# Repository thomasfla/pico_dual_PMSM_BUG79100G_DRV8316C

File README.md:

# pico_dual_PMSM_BUG79100G_DRV8316C
Low cost PMSM using RPI Pico, external ADC and integrated mos+driver+current sensing.

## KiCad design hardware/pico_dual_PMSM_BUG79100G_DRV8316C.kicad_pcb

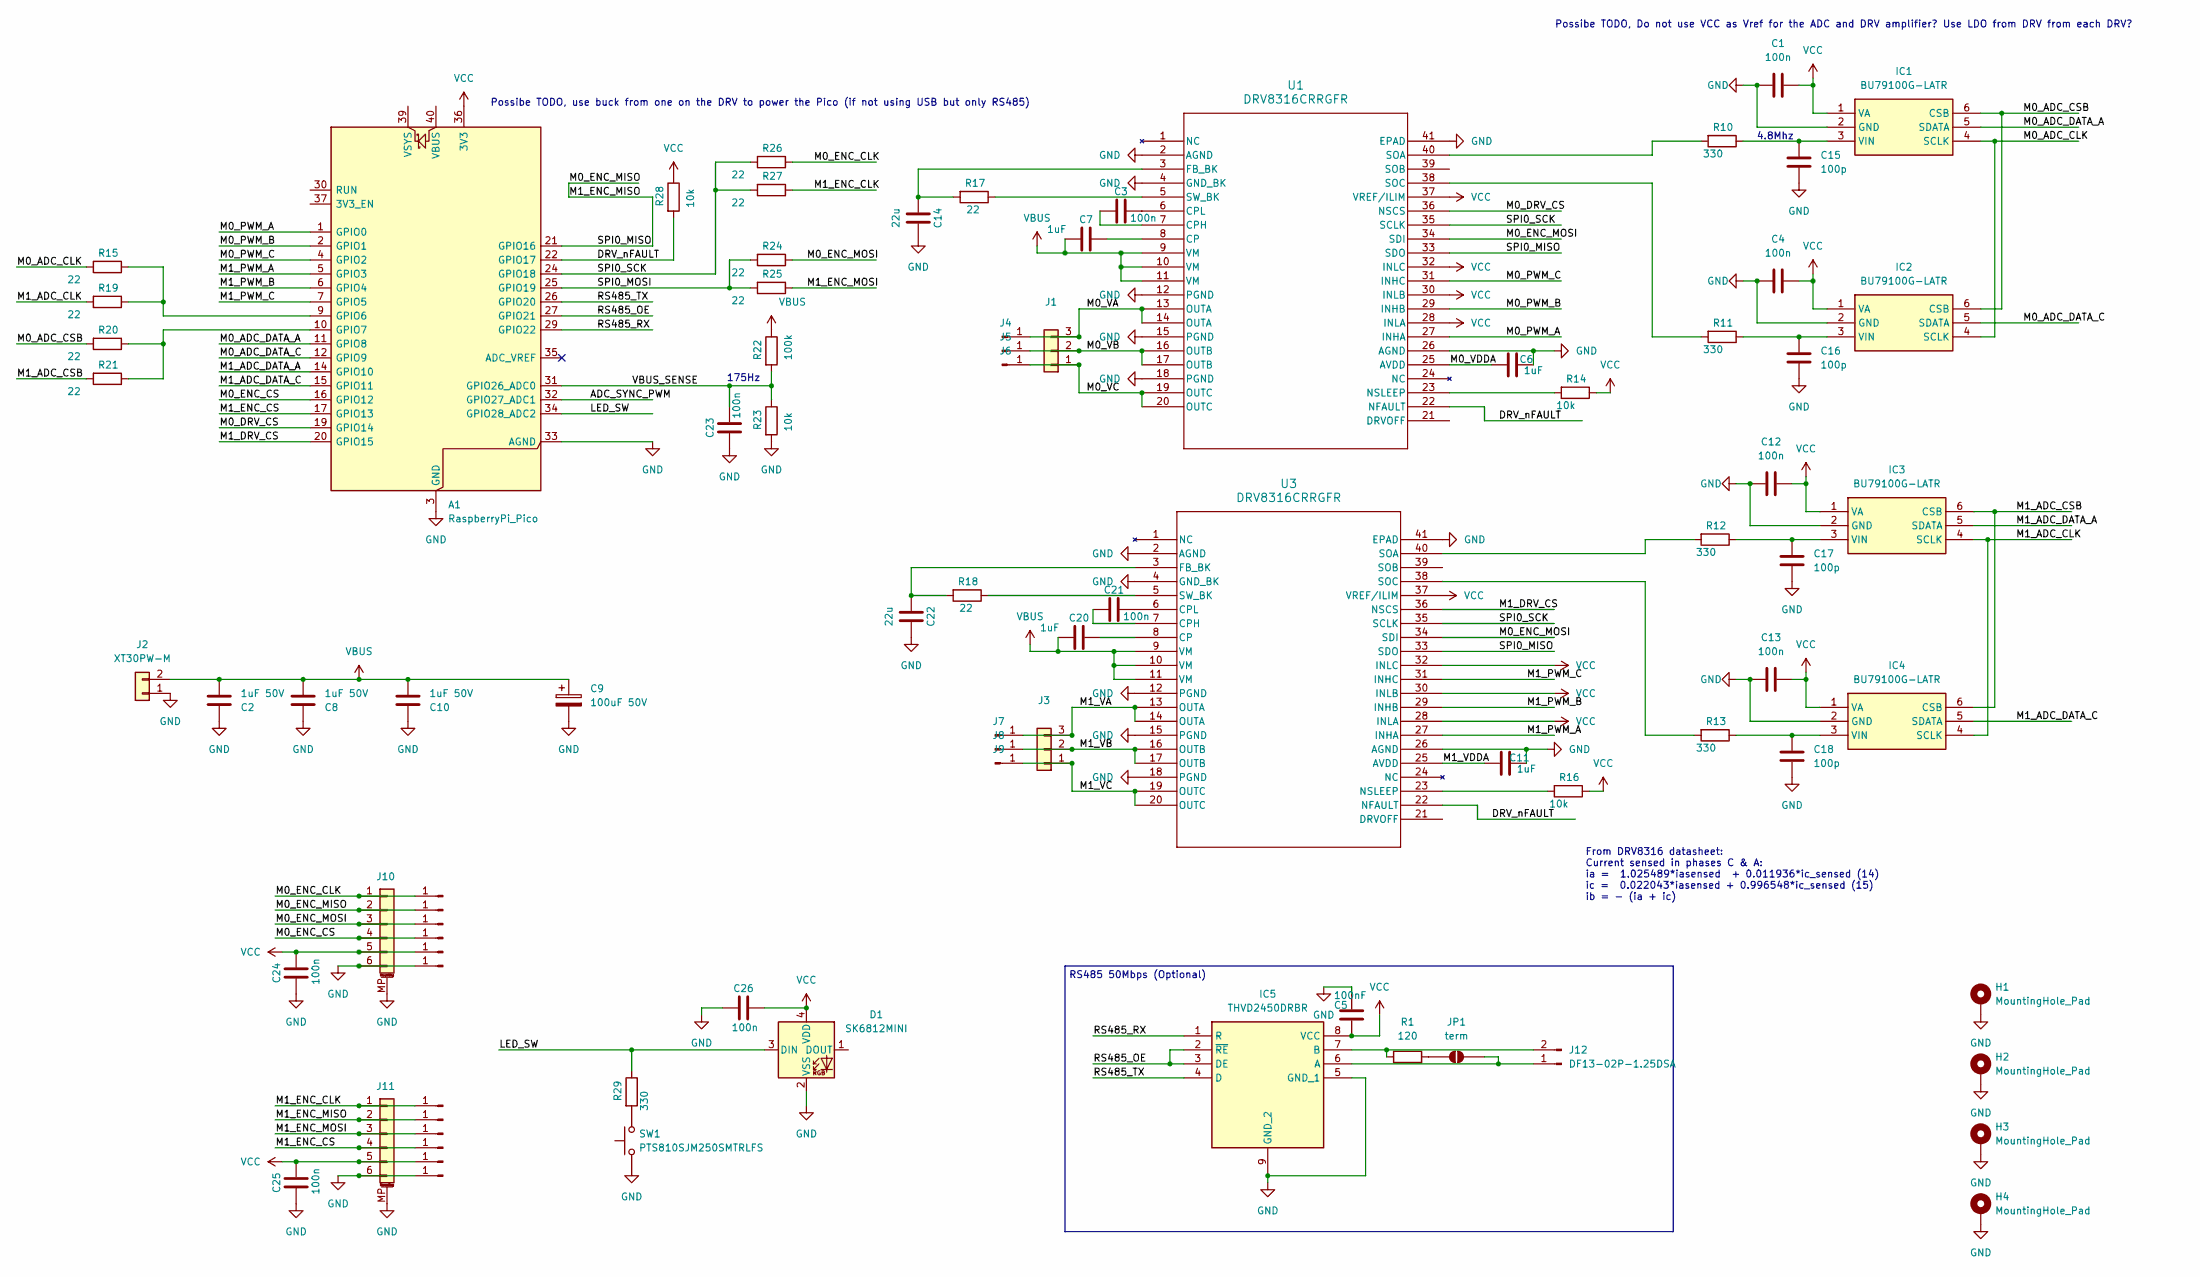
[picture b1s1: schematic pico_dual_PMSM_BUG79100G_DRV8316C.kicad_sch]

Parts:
A1: RaspberryPi_Pico; RaspberryPi_Pico_Common_Unspecified; Mouser Part Number 358-SC1631; mouser 358-SC1631
C1, C3, C4, C12, C13, C21, C23, C24, C25, C26: 100n; C_0402_1005Metric; Mouser Part Number 187-CL05B104KB5NNWC; mouser 187-CL05B104KB5NNWC
C2, C8, C10: 1uF 50V; C_1206_3216Metric; Mouser Part Number 80-C1206F105M5RAUTO
C5: 100nF; C_0603_1608Metric; Mouser Part Number 81-GRM188R72A104KA35; mouser 81-GRM188R72A104KA35
C6, C7, C11, C20: 1uF; C_0402_1005Metric; Mouser Part Number 187-CL05A105KO5NNNC; mouser 187-CL05A105KO5NNNC
C9: 100uF 50V; CP_Radial_D10.0mm_P5.00mm; Mouser Part Number 594-MAL219051101E3
C14, C22: 22u; C_0805_2012Metric; Mouser Part Number 80-C0805C226M8P; mouser 80-C0805C226M8P
C15, C16, C17, C18: 100p; C_0402_1005Metric; Mouser Part Number 81-GRM1555C1H101JA1J
D1: SK6812MINI; LED_SK6812MINI_PLCC4_3.5x3.5mm_P1.75mm
H1, H2, H3, H4: MountingHole_Pad; MountingHole_2.5mm_Pad_Via
IC1, IC2, IC3, IC4: BU79100G-LATR; SOT95P280X125-6N; MPN BU79100G-LATR; mouser 755-BU79100G-LATR
IC5: THVD2450DRBR; SON65P300X300X100-9N; MPN THVD2450DRBR; mouser 595-THVD2450DRBR
J1, J3: PinHeader_1x03_P2.54mm_Horizontal
J2: XT30PW-M; AMASS_XT30PW-M_1x02_P2.50mm_Horizontal
J4, J5, J6, J7, J8, J9: SolderWirePad_1x01_SMD_2x4mm
J10, J11: BM06B-SRSS-TB; JST_SH_BM06B-SRSS-TB_1x06-1MP_P1.00mm_Vertical; Mouser Part Number 306-6BSRSSTBLPP; mouser 306-6BSRSSTBLPP
J12: DF13-02P-1.25DSA; Hirose_DF13-02P-1.25DSA_1x02_P1.25mm_Vertical
J14, J15, J16, J17, J18, J19, J20, J21, J22, J23, J24, J25: Conn_01x01_Pin; SolderWirePad_1x01_SMD_1x2mm
JP1: term; SolderJumper-2_P1.3mm_Open_RoundedPad1.0x1.5mm
R1: 120; R_0603_1608Metric; Mouser Part Number 603-RC0603FR-07120RL; mouser 603-RC0603FR-07120RL
R10, R11, R12, R13, R29: 330; R_0402_1005Metric; Mouser Part Number 603-RC0402FR-07330RL
R14, R16, R23, R28: 10k; R_0402_1005Metric; Mouser Part Number 603-RC0402FR-0710KL
R15, R17, R18, R19, R20, R21, R24, R25, R26, R27: 22; R_0402_1005Metric; Mouser Part Number 603-RC0402FR-0722RL
R22: 100k; R_0402_1005Metric; Mouser Part Number 603-RC0402FR-07100KL
SW1: PTS810SJM250SMTRLFS; SW_SPST_PTS810; Mouser Part Number 611-PTS810SJM250SMTR; mouser 611-PTS810SJM250SMTR
U1, U3: DRV8316CRRGFR; VQFN40_RGF_TEX; Mouser Part Number 595-DRV8316CRRGFR; mouser 595-DRV8316CRRGFR

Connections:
/ADC_SYNC_PWM: A1.32 (GPIO27_ADC1)
/DRV_nFAULT: A1.22 (GPIO17), R28.2, U1.22 (NFAULT), U3.22 (NFAULT)
/LED_SW: A1.34 (GPIO28_ADC2), D1.3 (DIN), R29.1
/M0_ADC_CLK: IC1.4 (SCLK), IC2.4 (SCLK), R15.2
/M0_ADC_CSB: IC1.6 (CSB), IC2.6 (CSB), R20.2
/M0_ADC_DATA_A: A1.11 (GPIO8), IC1.5 (SDATA)
/M0_ADC_DATA_C: A1.12 (GPIO9), IC2.5 (SDATA)
/M0_DRV_CS: A1.19 (GPIO14), U1.36 (NSCS)
/M0_ENC_CLK: J10.1, J14.1 (Pin_1_1), R26.1
/M0_ENC_CS: A1.16 (GPIO12), J10.4, J17.1 (Pin_1_1)
/M0_ENC_MISO: A1.21 (GPIO16), J10.2, J11.2, J15.1 (Pin_1_1), J21.1 (Pin_1_1), U1.33 (SDO), U3.33 (SDO)
/M0_ENC_MOSI: J10.3, J16.1 (Pin_1_1), R24.1, U1.34 (SDI), U3.34 (SDI)
/M0_PWM_A: A1.1 (GPIO0), U1.27 (INHA)
/M0_PWM_B: A1.2 (GPIO1), U1.29 (INHB)
/M0_PWM_C: A1.4 (GPIO2), U1.31 (INHC)
/M0_VA: J1.3, J4.1 (Pin_1_1), U1.13 (OUTA), U1.14 (OUTA)
/M0_VB: J1.2, J5.1 (Pin_1_1), U1.16 (OUTB), U1.17 (OUTB)
/M0_VC: J1.1, J6.1 (Pin_1_1), U1.19 (OUTC), U1.20 (OUTC)
/M0_VDDA: C6.1, U1.25 (AVDD)
/M1_ADC_CLK: IC3.4 (SCLK), IC4.4 (SCLK), R19.2
/M1_ADC_CSB: IC3.6 (CSB), IC4.6 (CSB), R21.2
/M1_ADC_DATA_A: A1.14 (GPIO10), IC3.5 (SDATA)
/M1_ADC_DATA_C: A1.15 (GPIO11), IC4.5 (SDATA)
/M1_DRV_CS: A1.20 (GPIO15), U3.36 (NSCS)
/M1_ENC_CLK: J11.1, J18.1 (Pin_1_1), R27.1
/M1_ENC_CS: A1.17 (GPIO13), J11.4, J23.1 (Pin_1_1)
/M1_ENC_MOSI: J11.3, J22.1 (Pin_1_1), R25.1
/M1_PWM_A: A1.5 (GPIO3), U3.27 (INHA)
/M1_PWM_B: A1.6 (GPIO4), U3.29 (INHB)
/M1_PWM_C: A1.7 (GPIO5), U3.31 (INHC)
/M1_VA: J3.3, J7.1 (Pin_1_1), U3.13 (OUTA), U3.14 (OUTA)
/M1_VB: J3.2, J8.1 (Pin_1_1), U3.16 (OUTB), U3.17 (OUTB)
/M1_VC: J3.1, J9.1 (Pin_1_1), U3.19 (OUTC), U3.20 (OUTC)
/M1_VDDA: C11.1, U3.25 (AVDD)
/RS485_OE: A1.27 (GPIO21), IC5.2 (~RE), IC5.3 (DE)
/RS485_RX: A1.29 (GPIO22), IC5.1 (R)
/RS485_TX: A1.26 (GPIO20), IC5.4 (D)
/SPI0_MOSI: A1.25 (GPIO19), R24.2, R25.2
/SPI0_SCK: A1.24 (GPIO18), R26.2, R27.2, U1.35 (SCLK), U3.35 (SCLK)
/VBUS_SENSE: A1.31 (GPIO26_ADC0), C23.2, R22.2, R23.1
GND: A1.3 (GND), A1.8 (GND), A1.13 (GND), A1.18 (GND), A1.23 (GND), A1.28 (GND), A1.33 (AGND), A1.38 (GND), C1.1, C2.1, C4.1, C5.1, C6.2, C8.1, C9.2, C10.1, C11.2, C12.1, C13.1, C14.2, C15.2, C16.2, C17.2, C18.2, C22.2, C23.1, C24.1, C25.1, C26.1, D1.2 (VSS), H1.1 (1_1), H2.1 (1_1), H3.1 (1_1), H4.1 (1_1), IC1.2 (GND), IC2.2 (GND), IC3.2 (GND), IC4.2 (GND), IC5.5 (GND_1), IC5.9 (GND_2), J2.1, J10.6, J10.MP (MountPin), J11.6, J11.MP (MountPin), J20.1 (Pin_1_1), J25.1 (Pin_1_1), R23.2, SW1.1, U1.2 (AGND), U1.4 (GND_BK), U1.12 (PGND), U1.15 (PGND), U1.18 (PGND), U1.26 (AGND), U1.41 (EPAD), U3.2 (AGND), U3.4 (GND_BK), U3.12 (PGND), U3.15 (PGND), U3.18 (PGND), U3.26 (AGND), U3.41 (EPAD)
unnamed: A1.9 (GPIO6), R15.1, R19.1
unnamed: A1.10 (GPIO7), R20.1, R21.1
unnamed: C15.1, IC1.3 (VIN), R10.1
unnamed: C16.1, IC2.3 (VIN), R11.1
unnamed: C17.1, IC3.3 (VIN), R12.1
unnamed: C18.1, IC4.3 (VIN), R13.1
unnamed: IC5.6 (A), J12.1, JP1.2 (B)
unnamed: IC5.7 (B), J12.2, R1.1
unnamed: JP1.1 (A), R1.2
unnamed: R29.2, SW1.2
unnamed: C7.2, U1.8 (CP)
unnamed: C3.1, U1.7 (CPH)
unnamed: C3.2, U1.6 (CPL)
unnamed: C14.1, R17.2, U1.3 (FB_BK)
unnamed: R14.2, U1.23 (NSLEEP)
unnamed: R10.2, U1.40 (SOA)
unnamed: R11.2, U1.38 (SOC)
unnamed: R17.1, U1.5 (SW_BK)
unnamed: C20.2, U3.8 (CP)
unnamed: C21.1, U3.7 (CPH)
unnamed: C21.2, U3.6 (CPL)
unnamed: C22.1, R18.2, U3.3 (FB_BK)
unnamed: R16.2, U3.23 (NSLEEP)
unnamed: R12.2, U3.40 (SOA)
unnamed: R13.2, U3.38 (SOC)
unnamed: R18.1, U3.5 (SW_BK)
VBUS: C2.2, C7.1, C8.2, C9.1, C10.2, C20.1, J2.2, R22.1, U1.9 (VM), U1.10 (VM), U1.11 (VM), U3.9 (VM), U3.10 (VM), U3.11 (VM)
VCC: A1.36 (3V3), C1.2, C4.2, C5.2, C12.2, C13.2, C24.2, C25.2, C26.2, D1.4 (VDD), IC1.1 (VA), IC2.1 (VA), IC3.1 (VA), IC4.1 (VA), IC5.8 (VCC), J10.5, J11.5, J19.1 (Pin_1_1), J24.1 (Pin_1_1), R14.1, R16.1, R28.1, U1.28 (INLA), U1.30 (INLB), U1.32 (INLC), U1.37 (VREF/ILIM), U3.28 (INLA), U3.30 (INLB), U3.32 (INLC), U3.37 (VREF/ILIM)

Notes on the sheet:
4.8Mhz
175Hz
RS485 50Mbps (Optional)
Possibe TODO, Do not use VCC as Vref for the ADC and DRV amplifier? Use LDO from DRV from each DRV?
Possibe TODO, use buck from one on the DRV to power the Pico (if not using USB but only RS485)
From DRV8316 datasheet: Current sensed in phases C & A: ia = 1.025489*iasensed + 0.011936*ic_sensed (14) ic = 0.022043*iasensed + 0.996548*ic_sensed (15) ib = − (ia + ic)

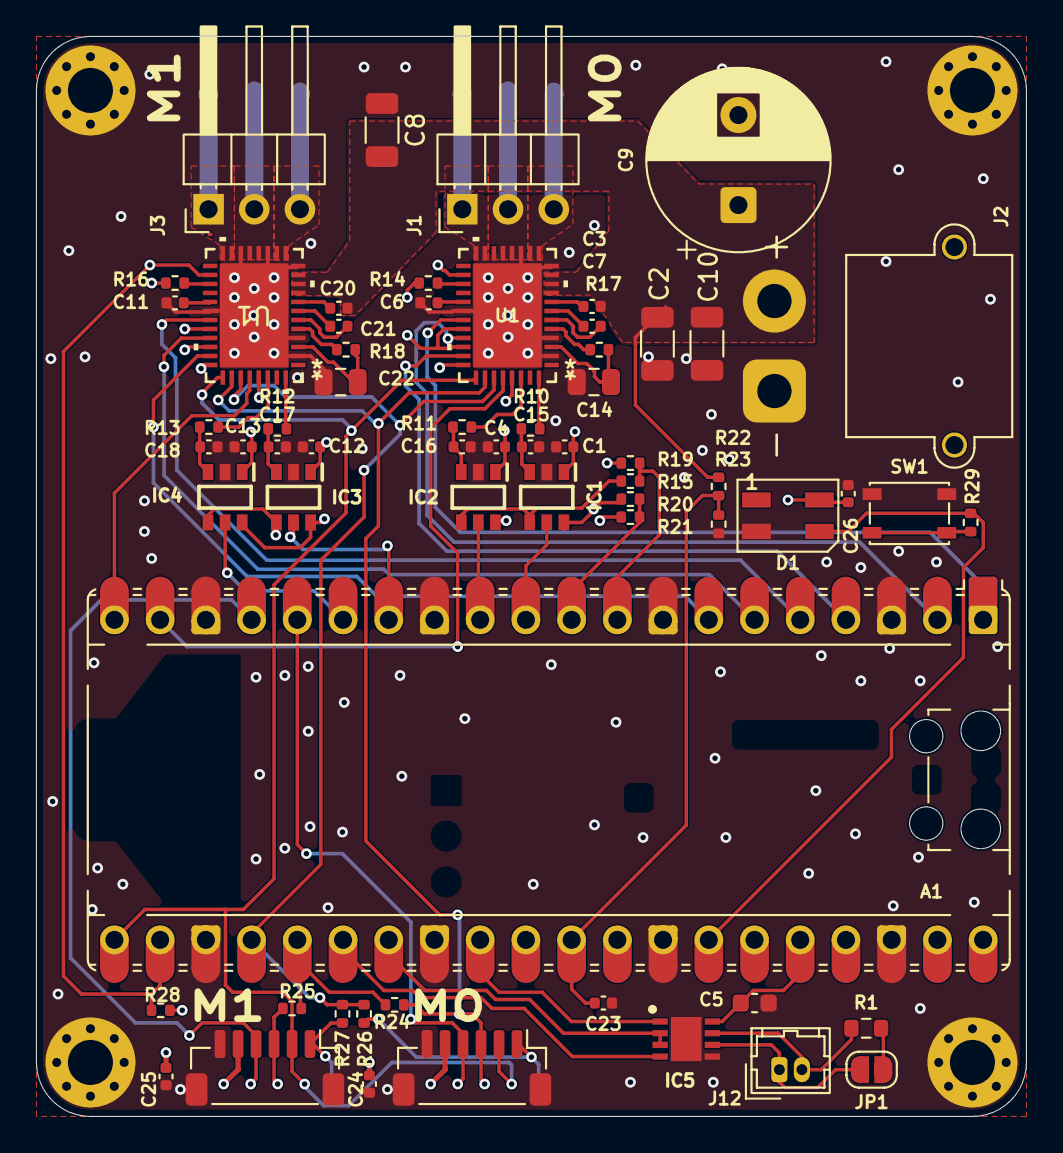
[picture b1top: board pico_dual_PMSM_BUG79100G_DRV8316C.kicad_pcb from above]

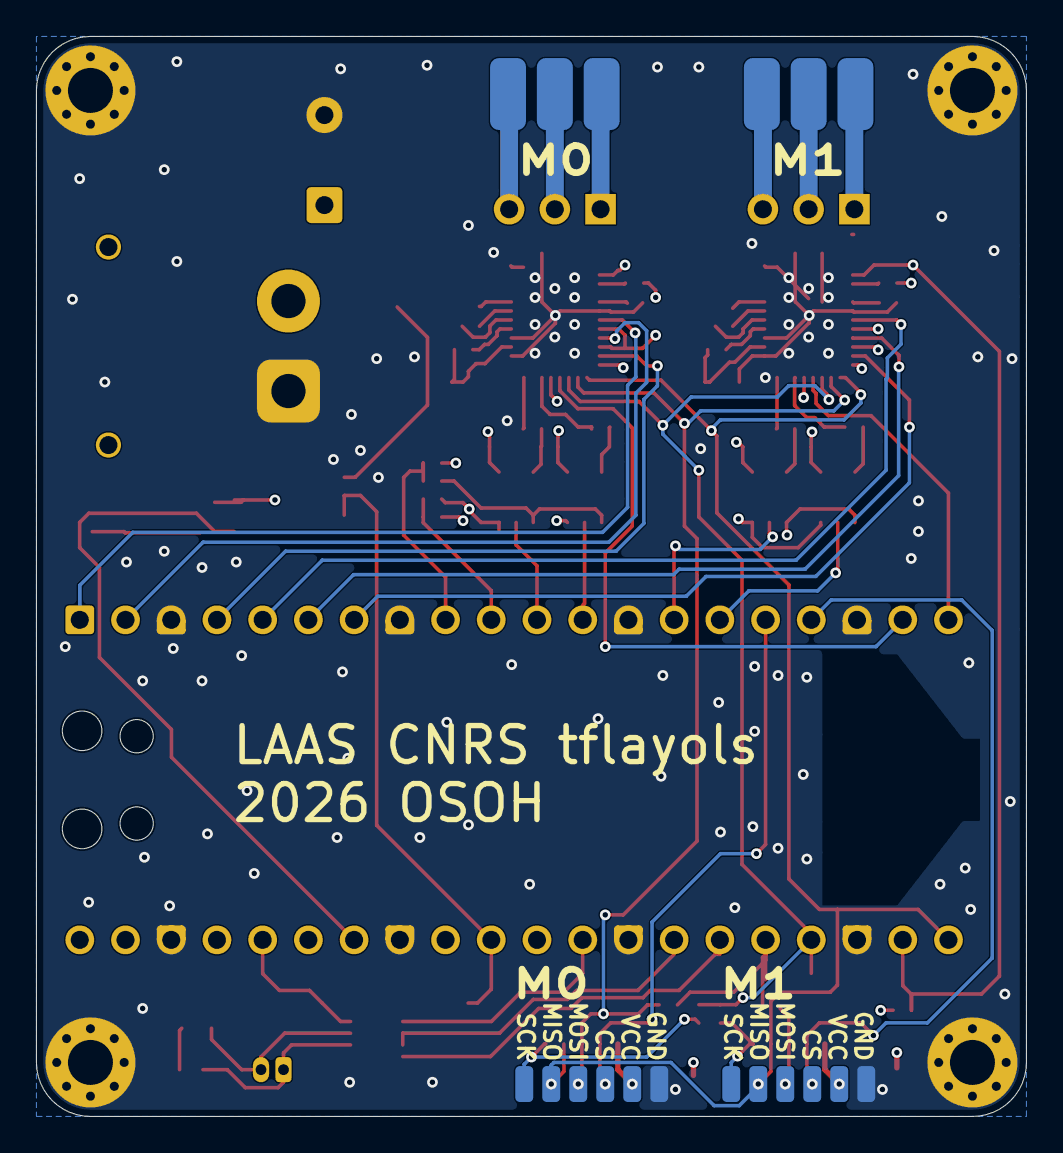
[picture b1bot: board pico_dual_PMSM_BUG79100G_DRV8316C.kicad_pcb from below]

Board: 4 copper layers, 55.0 x 60.0 mm, 85 parts (18 on the bottom side), 68 nets.

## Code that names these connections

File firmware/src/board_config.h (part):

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#include <Arduino.h>
#include <SimpleFOC.h>

#define GPIO_M0_PWM_A 0
#define GPIO_M0_PWM_B 1
#define GPIO_M0_PWM_C 2
#define GPIO_M1_PWM_A 3
#define GPIO_M1_PWM_B 4
#define GPIO_M1_PWM_C 5

#define GPIO_ADC_SCK 6
#define GPIO_ADC_CSB 7
#define GPIO_M0_ADC_DATA_A 8
#define GPIO_M0_ADC_DATA_C 9
#define GPIO_M1_ADC_DATA_A 10
#define GPIO_M1_ADC_DATA_C 11

#define GPIO_M0_ENC_CS 12
#define GPIO_M1_ENC_CS 13
#define GPIO_M0_DRV_CS 14
#define GPIO_M1_DRV_CS 15
#define GPIO_SPI0_MISO 16
#define GPIO_DRV_Mx_nFAULT 17
#define GPIO_SPI0_CLK 18
#define GPIO_SPI0_MOSI 19
#define GPIO_PICO_LED 25
#define GPIO_VBUS_SENSE 26
#define GPIO_ADC_SYNC_PWM 27
#define GPIO_ESTOP 28

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
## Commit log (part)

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2026-06-01 Add fils
